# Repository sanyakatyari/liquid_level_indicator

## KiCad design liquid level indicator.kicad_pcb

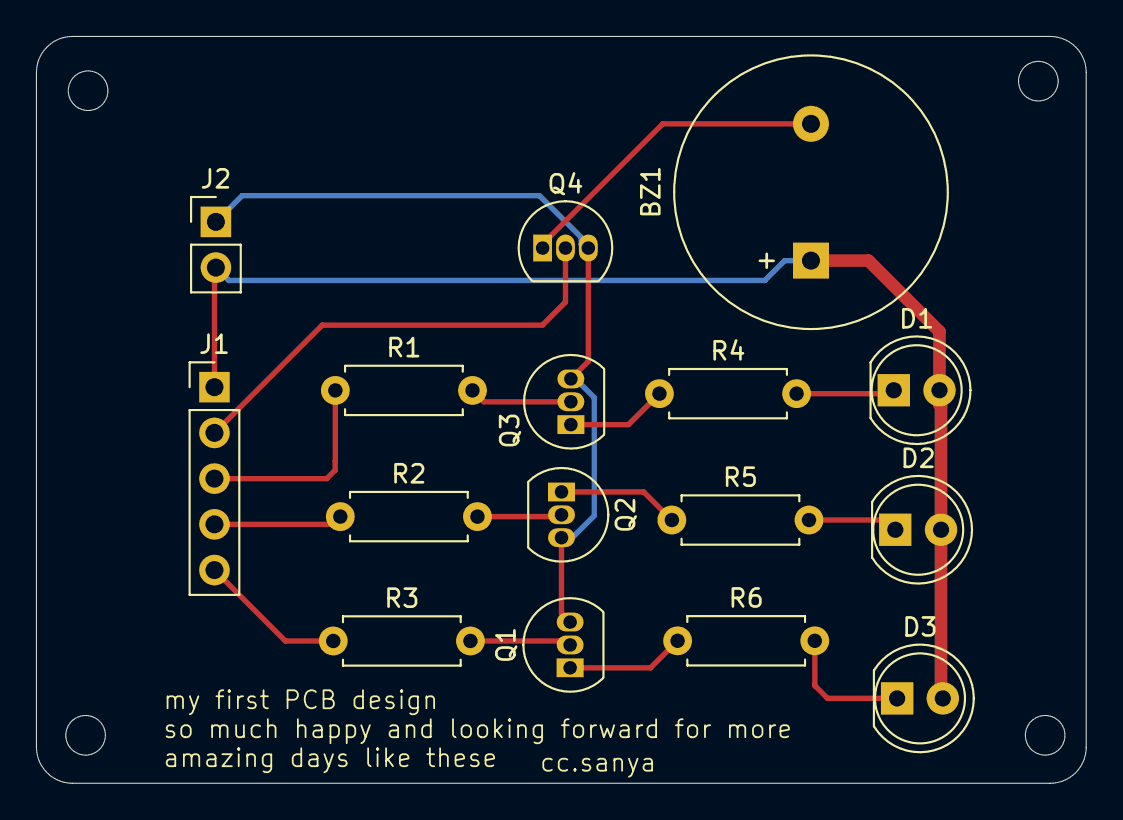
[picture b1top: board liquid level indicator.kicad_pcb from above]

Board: 2 copper layers, 58.3 x 41.5 mm, 16 parts (0 on the bottom side), 16 nets.

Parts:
BZ1: Buzzer; Buzzer_15x7.5RM7.6
D1, D2, D3: LED; LED_D5.0mm
J1: Conn_01x05_Pin; PinHeader_1x05_P2.54mm_Vertical
J2: Conn_01x02_Pin; PinHeader_1x02_P2.54mm_Vertical
Q1, Q2, Q3, Q4: BC547; TO-92_Inline
R1, R2, R3: 100; R_Axial_DIN0207_L6.3mm_D2.5mm_P7.62mm_Horizontal
R4, R5, R6: 1K; R_Axial_DIN0207_L6.3mm_D2.5mm_P7.62mm_Horizontal

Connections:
+9V: BZ1.1 (+), D1.2 (A), D2.2 (A), D3.2 (A), J1.1, J2.2
GND: J2.1, Q1.3 (E), Q2.3 (E), Q3.3 (E), Q4.3 (E)
unnamed: BZ1.2 (-), Q4.1 (C)
unnamed: D1.1 (K), R4.2
unnamed: D2.1 (K), R5.2
unnamed: D3.1 (K), R6.2
unnamed: J1.2, Q4.2 (B)
unnamed: J1.3, R1.1
unnamed: J1.4, R2.1
unnamed: J1.5, R3.1
unnamed: Q1.2 (B), R3.2
unnamed: Q1.1 (C), R6.1
unnamed: Q2.2 (B), R2.2
unnamed: Q2.1 (C), R5.1
unnamed: Q3.2 (B), R1.2
unnamed: Q3.1 (C), R4.1
